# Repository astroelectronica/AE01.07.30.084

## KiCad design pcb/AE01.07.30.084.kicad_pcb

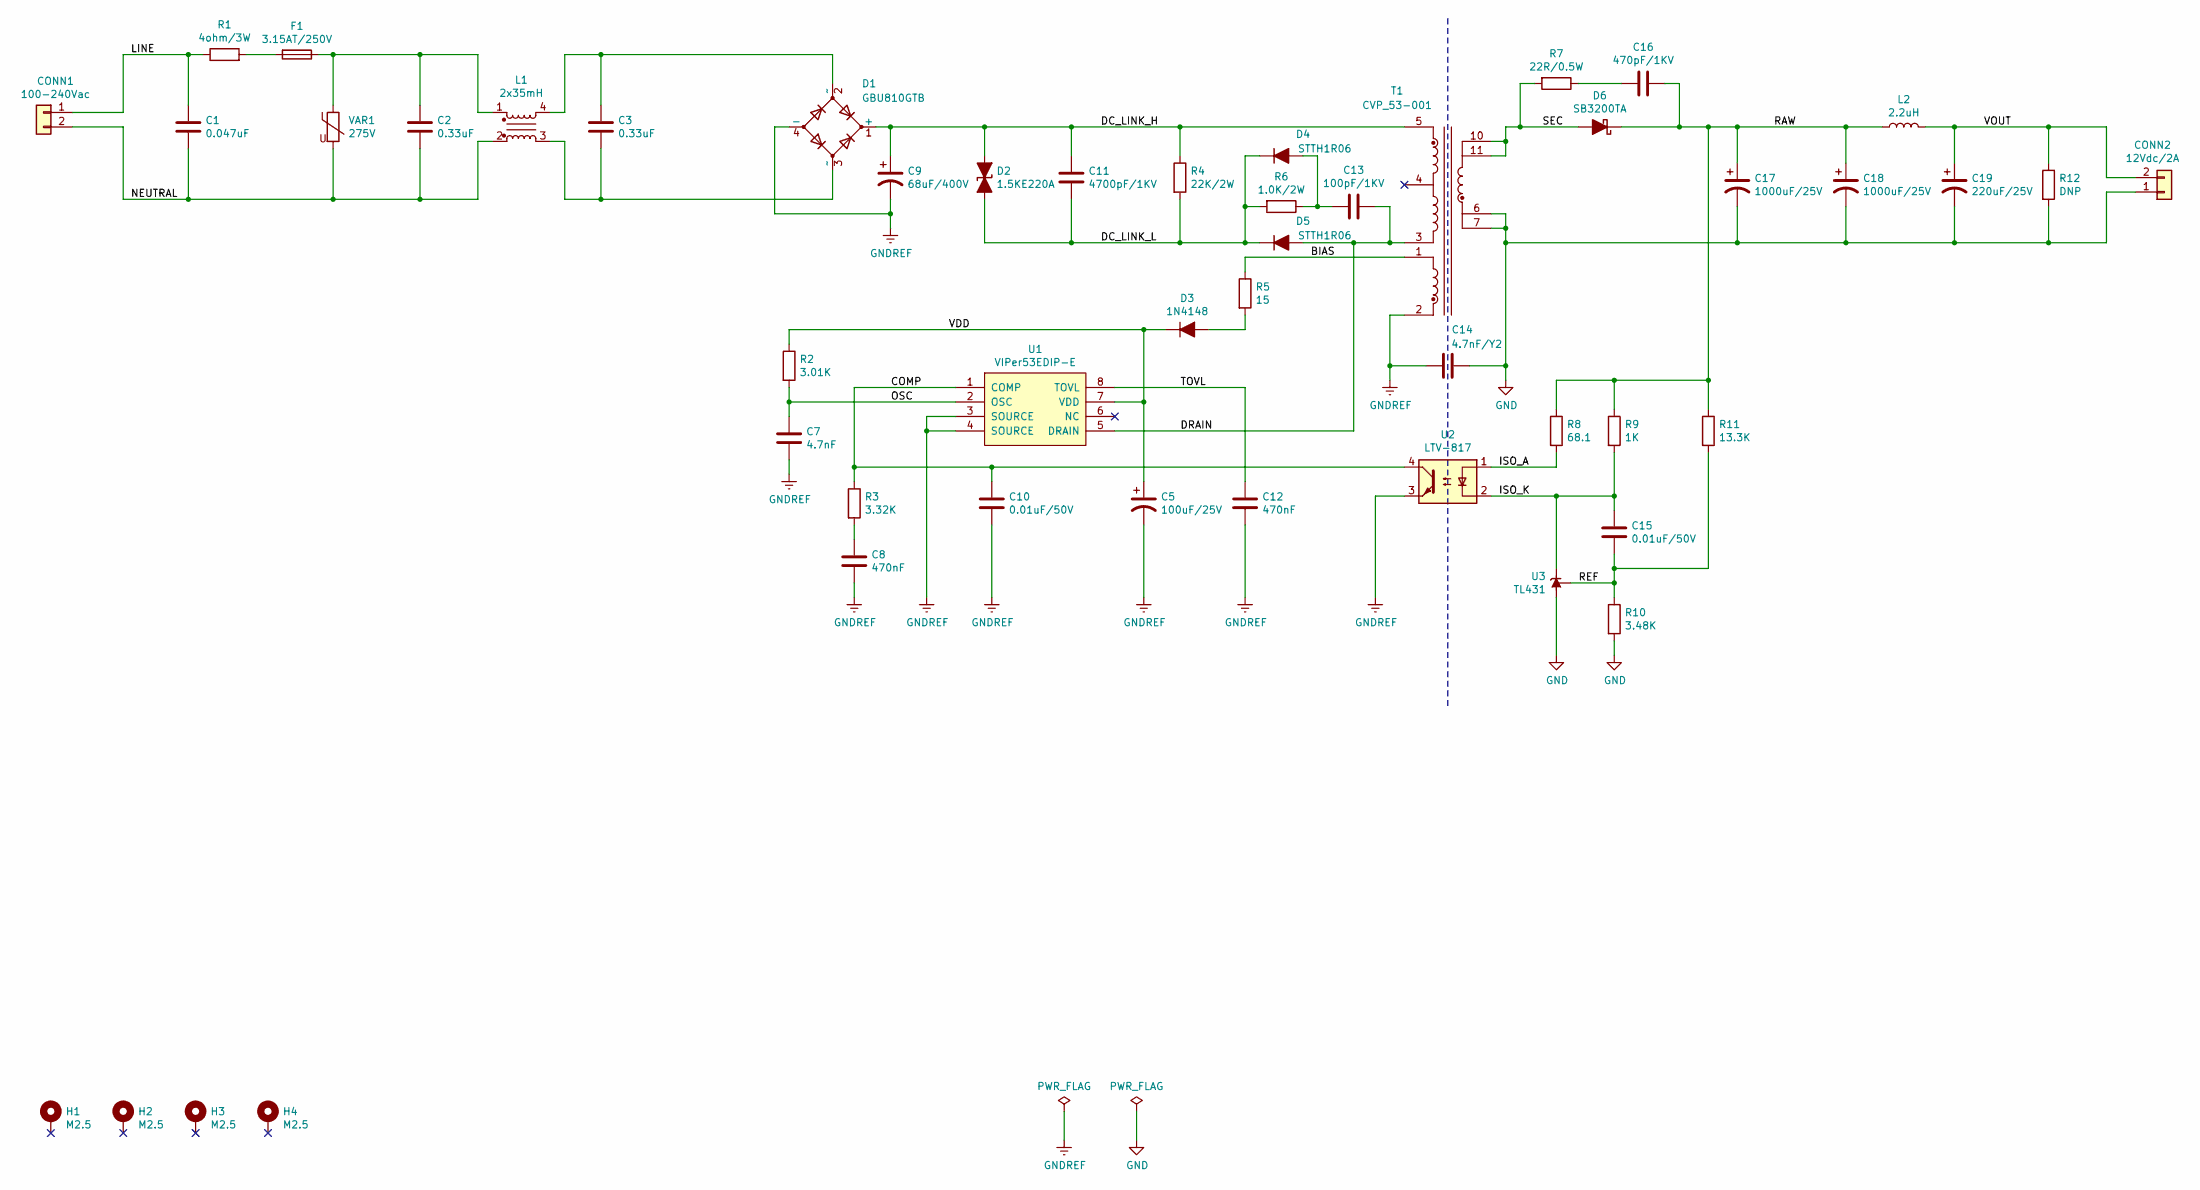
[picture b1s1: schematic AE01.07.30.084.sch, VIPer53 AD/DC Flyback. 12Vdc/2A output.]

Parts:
C1: 0.047uF; C_Rect_L13.0mm_W4.0mm_P10.00mm_FKS3_FKP3_MKS4; MPN BFC233921473
C2, C3: 0.33uF; C_Rect_L18.0mm_W9.0mm_P15.00mm_FKS3_FKP3; MPN BFC233920334
C5: 100uF/25V; CP_Radial_D6.3mm_P2.50mm; MPN ESK107M025AE3EA
C7: 4.7nF; C_Rect_L7.2mm_W2.5mm_P5.00mm_FKS2_FKP2_MKS2_MKP2; MPN MMK5472K63J01L4BULK
C8, C12: 470nF; C_Disc_D5.1mm_W3.2mm_P5.00mm; MPN K474Z20Y5VF5TH5
C9: 68uF/400V; CP_Radial_D16.0mm_P7.50mm; MPN 400BXW68MEFR16X25
C10, C15: 0.01uF/50V; C_Disc_D3.8mm_W2.6mm_P2.50mm; MPN C315C103K5R5TA7303
C11: 4700pF/1KV; C_Disc_D11.0mm_W5.0mm_P5.00mm; MPN CK45-B3AD472KYGNA
C13: 100pF/1KV; C_Disc_D7.5mm_W5.0mm_P5.00mm; MPN F101K25Y5RN63K5R
C14: 4.7nF/Y2; C_Disc_D12.5mm_W5.0mm_P7.50mm; MPN VY2472M49Y5US63V7
C16: 470pF/1KV; C_Disc_D12.5mm_W5.0mm_P7.50mm; MPN CC45SL3AD471JYGNA
C17, C18: 1000uF/25V; CP_Radial_D10.0mm_P5.00mm; MPN 25ZLH1000MEFCT810X23
C19: 220uF/25V; CP_Radial_D8.0mm_P5.00mm; MPN EEU-FR1E221B
CONN1: 100-240Vac; PhoenixContact_GMSTBA_2,5_2-G-7,62_1x02_P7.62mm_Horizontal; MPN 1728853
CONN2: 12Vdc/2A; PhoenixContact_GMSTBA_2,5_2-G-7,62_1x02_P7.62mm_Horizontal; MPN 1728853
D1: GBU810GTB; Diode_Bridge_Vishay_GBU; MPN GBU810GTB
D2: 1.5KE220A; D_DO-201_P15.24mm_Horizontal; MPN 1.5KE220A
D3: 1N4148; D_DO-35_SOD27_P7.62mm_Horizontal; MPN 1N4148TR
D4, D5: STTH1R06; D_DO-41_SOD81_P10.16mm_Horizontal; MPN STTH1R06RL
D6: SB3200TA; D_DO-201AD_P15.24mm_Horizontal; MPN SB3200TA
F1: 3.15AT/250V; Fuseholder_Cylinder-5x20mm_Schurter_0031_8201_Horizontal_Op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; MPN 0031.8201
H1, H2, H3, H4: M2.5; MountingHole_2.7mm_Pad_Via
L1: 2x35mH; L_CommonMode_Wuerth_WE-CMB-NC; MPN 7448040435
L2: 2.2uH; L_Radial_D9.5mm_P5.00mm_Fastron_07HVP; MPN AIUR-03-2R2M
R1: 4ohm/3W; R_Axial_DIN0614_L14.3mm_D5.7mm_P20.32mm_Horizontal; MPN WW3FT4R00
R2: 3.01K; R_Axial_DIN0207_L6.3mm_D2.5mm_P10.16mm_Horizontal; MPN RNF14FTD3K01
R3: 3.32K; R_Axial_DIN0207_L6.3mm_D2.5mm_P10.16mm_Horizontal; MPN RNF14FTD3K32
R4: 22K/2W; R_Axial_DIN0516_L15.5mm_D5.0mm_P25.40mm_Horizontal; MPN RSF2JT22K0
R5: 15; R_Axial_DIN0207_L6.3mm_D2.5mm_P10.16mm_Horizontal; MPN RNF14FTD15R0
R6: 1.0K/2W; R_Axial_DIN0516_L15.5mm_D5.0mm_P25.40mm_Horizontal; MPN RSF2JT1K00
R7: 22R/0.5W; R_Axial_DIN0309_L9.0mm_D3.2mm_P12.70mm_Horizontal; MPN CF12JT22R0
R8: 68.1; R_Axial_DIN0207_L6.3mm_D2.5mm_P10.16mm_Horizontal; MPN RNF14FTD68R1
R9: 1K; R_Axial_DIN0207_L6.3mm_D2.5mm_P10.16mm_Horizontal; MPN RNF14FTD1K00
R10: 3.48K; R_Axial_DIN0207_L6.3mm_D2.5mm_P10.16mm_Horizontal; MPN RNF14FTD3K48
R11: 13.3K; R_Axial_DIN0207_L6.3mm_D2.5mm_P10.16mm_Horizontal; MPN RNF14FTD13K3
R12: DNP; R_Axial_DIN0207_L6.3mm_D2.5mm_P10.16mm_Horizontal
T1: CVP_53-001; MPN CVP 53-001
U1: VIPer53EDIP-E; DIP-8_W7.62mm; MPN VIPER53EDIP-E
U2: LTV-817; DIP-4_W7.62mm; MPN LTV-817
U3: TL431; TO-92_Inline_Wide; MPN TL431CLPRE3
VAR1: 275V; RV_Disc_D15.5mm_W3.9mm_P7.5mm; MPN B72214S2271K151

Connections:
/BIAS: R5.1, T1.1
/COMP: C10.1, R3.1, U1.1 (COMP), U2.4
/DC_LINK_H: C9.1, C11.1, D1.1 (+), D2.2 (A2), R4.1, T1.5
/DC_LINK_L: C11.2, D2.1 (A1), D4.1 (K), D5.1 (K), R4.2, R6.2
/DRAIN: C13.1, D5.2 (A), T1.3, U1.5 (DRAIN)
/ISO_A: R8.2, U2.1
/ISO_K: C15.1, R9.2, U2.2, U3.3 (K)
/LINE: C1.1, CONN1.1, R1.1
/NEUTRAL: C1.2, C2.2, CONN1.2, L1.2, VAR1.2
/OSC: C7.1, R2.2, U1.2 (OSC)
/RAW: C16.1, C17.1, C18.1, D6.1 (K), L2.1, R8.1, R9.1, R11.1
/REF: C15.2, R10.1, R11.2, U3.1 (REF)
/SEC: D6.2 (A), R7.2, T1.10, T1.11
/TOVL: C12.1, U1.8 (TOVL)
/VDD: C5.1, D3.1 (K), R2.1, U1.7 (VDD)
/VOUT: C19.1, CONN2.2, L2.2, R12.1
GND: C14.1, C17.2, C18.2, C19.2, CONN2.1, R10.2, R12.2, T1.6, T1.7, U3.2 (A)
GNDREF: C5.2, C7.2, C8.2, C9.2, C10.2, C12.2, C14.2, D1.4 (-), T1.2, U1.3 (SOURCE), U1.4 (SOURCE), U2.3
unnamed: C2.1, F1.1, L1.1, VAR1.1
unnamed: C3.1, D1.2 (~~), L1.4
unnamed: C3.2, D1.3 (~~), L1.3
unnamed: C8.1, R3.2
unnamed: C13.2, D4.2 (A), R6.1
unnamed: C16.2, R7.1
unnamed: D3.2 (A), R5.2
unnamed: F1.2, R1.2

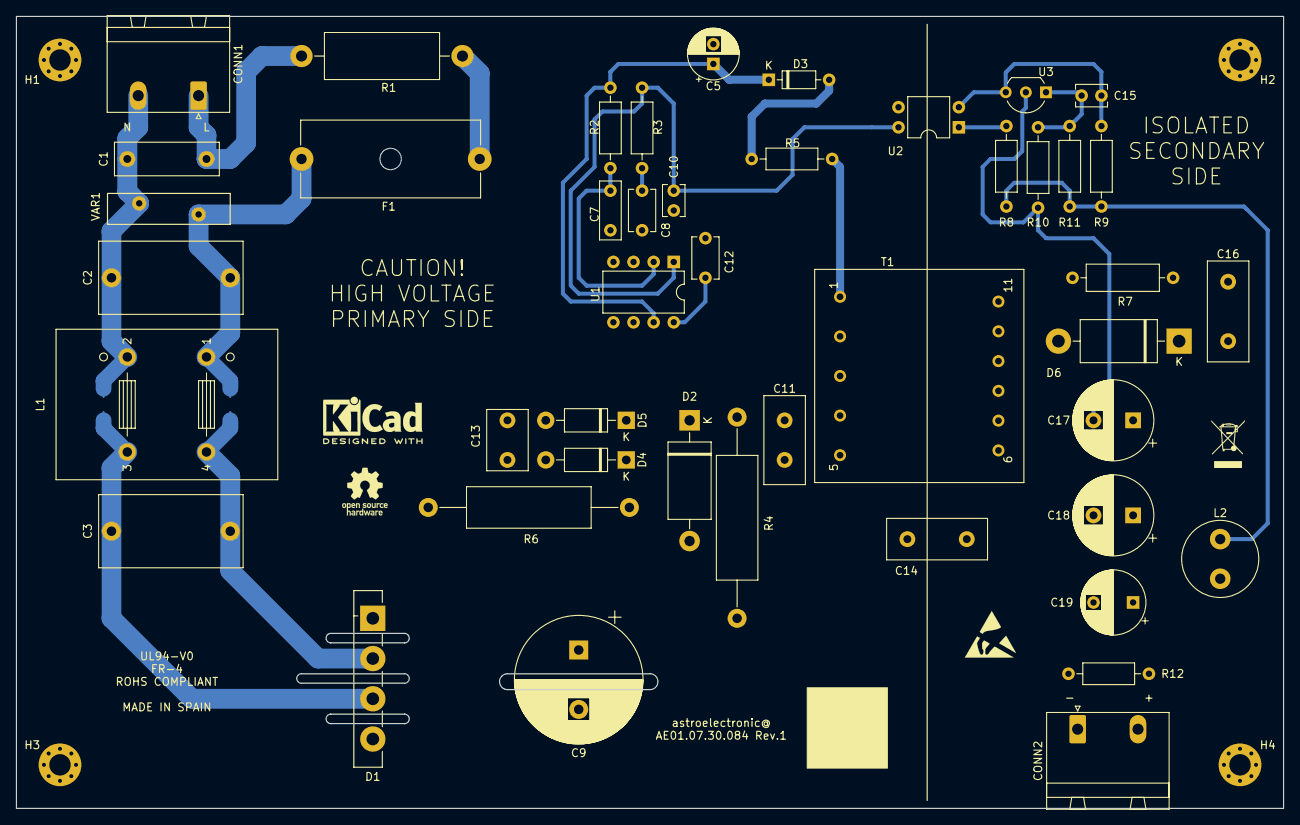
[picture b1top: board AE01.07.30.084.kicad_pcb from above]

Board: 2 copper layers, 160.0 x 100.0 mm, 49 parts (0 on the bottom side), 26 nets.
